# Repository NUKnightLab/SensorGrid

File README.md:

# Knight Lab SensorGridPM

Wireless particulate matter monitoring over LoRa networks

This is a version of the SensorGrid project that is specific to monitoring
particulate matter data (PM 2.5 and PM 10) and collecting that data over a
LoRa wireless network.

## Development

This code is structured for development in PlatformIO with its entry point set
to enable Arduino IDE compilation as well. See below for information about
compiling with the Arduino IDE.

### Dependencies

See the `lib_deps` section of the `platformio.ini` file

### Arduino IDE

Development is mostly done on PlatformIO (https://platformio.org/) but we do
occasional checks to ensure deployment on Arduino IDE. It should just work.

### Code Style

Please lint with cpplint before submitting code changes:

See this project's `CPPLINT.cfg` file for details about flags used for linting.
```
cpplint <SubProject>/*
```

We are making an effort to move toward the Google C++ style guide:
https://google.github.io/styleguide/cppguide.html

with some notable exceptions:

#### include subdirs not required

The requirement for specifying subdirs adds unnecessary complexity to project
maintenance. We use a relatively flat code structure within a given project,
thus includes will either be in the form `"file.h"` where file.h is in the
same directory or `<Library.h>` where Library is accessible on the compile path.

As a result, please lint with `--filter=-build/include_subdir`

#### naming conventions

 * Variables should be `snake_case`
 * Functions and methods should be `camelCase` (Not PascalCase)

## Troubleshooting

### The device goes into time-setting mode without pressing the time set button

The battery or solar subsystem must be plugged in for the device to start up in the standard runtime mode.

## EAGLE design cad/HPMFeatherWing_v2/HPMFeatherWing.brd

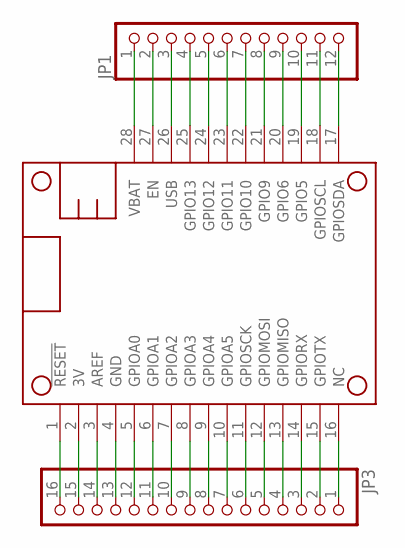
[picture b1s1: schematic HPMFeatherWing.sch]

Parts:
JP1: HEADER-1X1276MIL; 1X12_ROUND_76MIL
JP3: HEADER-1X16_76MIL; 1X16_ROUND_76MIL
MS1: FEATHERWING

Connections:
3V: JP3.15, MS1.2 (3V)
AREF: JP3.14, MS1.3 (AREF)
unnamed: JP1.2, MS1.27 (EN)
unnamed: JP3.1, MS1.16 (NC)
unnamed: JP1.4, MS1.25 (GPIO13)
unnamed: JP3.4, MS1.13 (GPIOMISO)
unnamed: JP3.5, MS1.12 (GPIOMOSI)
unnamed: JP3.6, MS1.11 (GPIOSCK)
unnamed: JP3.7, MS1.10 (GPIOA5)
unnamed: JP3.8, MS1.9 (GPIOA4)
unnamed: JP3.9, MS1.8 (GPIOA3)
unnamed: JP3.10, MS1.7 (GPIOA2)
unnamed: JP3.11, MS1.6 (GPIOA1)
unnamed: JP3.12, MS1.5 (GPIOA0)
unnamed: JP3.16, MS1.1 (!RESET)
unnamed: JP1.6, MS1.23 (GPIO11)
unnamed: JP1.7, MS1.22 (GPIO10)
unnamed: JP1.8, MS1.21 (GPIO9)
unnamed: JP1.9, MS1.20 (GPIO6)
unnamed: JP1.10, MS1.19 (GPIO5)
unnamed: JP1.11, MS1.18 (GPIOSCL)
unnamed: JP1.12, MS1.17 (GPIOSDA)
unnamed: JP3.3, MS1.14 (GPIORX)
unnamed: JP3.2, MS1.15 (GPIOTX)
unnamed: JP3.13, MS1.4 (GND)
unnamed: JP1.5, MS1.24 (GPIO12)
USB: JP1.3, MS1.26 (USB)
VBAT: JP1.1, MS1.28 (VBAT)

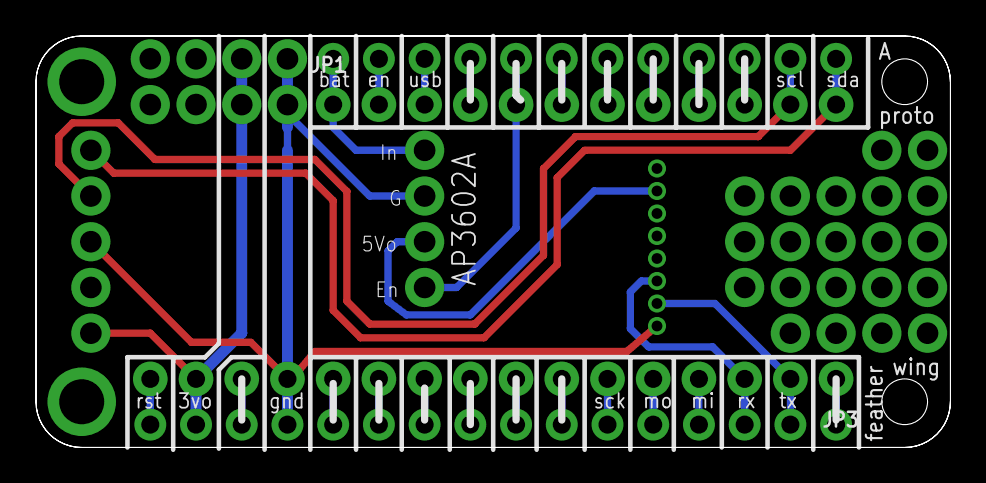
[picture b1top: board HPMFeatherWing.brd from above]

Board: 2 copper layers, 50.8 x 22.9 mm, 3 parts (0 on the bottom side), 28 nets.

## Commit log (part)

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2018-02-14 rtc begin first thing in setup
2018-02-14 reduce max nodes
2018-02-14 removed newline
2018-02-14 turn off wait for serial
2018-02-14 fix formatting of received message print
2018-02-14 log sent control
2018-02-14 removes blank line
2018-02-14 missing newline
2018-02-14 print NONE if no uncollected nodes
2018-02-14 logging cleanup
2018-02-15 fix pending node handling
2018-02-15 start of ditching auto-discovery
2018-02-15 no more auto-discovery
2018-02-16 buffer time for taking data samples
2018-02-16 don't use listen LED
2018-02-16 print out listen indicator; turns off data sampling and oled updates
2018-02-16 don't send control
2018-02-16 new SensorGrid.ino from scratch gets display working
2018-02-16 removes unused battery update thread (now in the display update)
2018-02-16 gets basic message send example working
2018-02-16 send period data collection request
2018-02-16 removes len from Message struct
2018-02-16 static malloc of the send Message space
2018-02-16 send collection request includes message id for each node - 0 for now
2018-02-16 adds array for last record ids
2018-02-16 try to fix iteration of dta record
2018-02-17 fix data iteration
2018-02-17 send new data back to 1
2018-02-17 try all next nodes before falling back to collector
2018-02-17 use low slow mode
2018-02-17 adds preferred routing order; replaces mesh router with static router
2018-02-17 routes to collector via from if no valid route exists
2018-02-17 print from before process_message call
2018-02-17 -> not .
2018-02-17 print add route to collector
2018-02-17 clear the receive buffer before receiving data
2018-02-17 turn off low and slow
2018-02-17 adds collector_process_message
2018-02-17 turns on cad
2018-02-18 spelling
2018-02-18 adds rh 1.8.2 tar
2018-02-18 timeout instead of protothread for display update
2018-02-18 set retries to 0
2018-02-18 send next activity after collection cycle
2018-02-18 turn off wait serial
2018-02-18 add self battery to new data
2018-02-18 rewrites node process data
2018-02-18 use constant MAX_NODES to create an ordered node array -- not a variable
2018-02-18 ordering is clobbering new data; use next_nodes for now
2018-02-18 include data type when adding battery level
2018-02-18 include max record id when adding self data
2018-02-18 track received record ids
2018-02-18 iterate to process data on collector
2018-02-18 update last dust sample time
2018-02-19 adds timestamp to sharp data
2018-02-19 use unixtime for dust timestamp
2018-02-19 loop through records for a node
2018-02-19 attempts to keep record collection under max data length
2018-02-19 comments removed
2018-02-19 print flags before send
2018-02-19 temp reduce max data length by 100
2018-02-19 change historical data head tracking
2018-02-19 set the max historical data id in the send data
2018-02-19 simplify historical data extraction
2018-02-19 check historical data based on the queue size
2018-02-19 turn off data sampling and oled updates
2018-02-19 increase hist data size
2018-02-19 debug printing of historical data traversal
2018-02-19 correct traversal index in log print
2018-02-19 missing condition check on printing out remaining historical data status
2018-02-19 print id of send to dest
2018-02-20 oled update back in
2018-02-20 attempt to avoid repeated data after a historical data shift
2018-02-20 missing in 50pct util case on collector
2018-02-20 fix string formatting of dust value print
2018-02-20 fix index of sharp dust struct in collector process
2018-02-20 use sharp dust struct for sending data
2018-02-20 fix record count and max id when adding sharp dust data
2018-02-20 insert sharp dust data as struct into new data
2018-02-20 struct for battery level
2018-02-20 50% data hist warn struct
2018-02-20 next activity seconds struct
2018-02-20 removes old approach to sending next activity
2018-02-20 attempt to manage collection via struct
2018-02-21 working on fixes to struct based data transfer. still not working right
2018-02-22 data record struct
2018-02-22 cleanup record set construction in send data col req
2018-02-25 move protocol.c into main program as protocol.cpp
2018-02-25 beginning of node handling of new protocol format
2018-02-27 basic node message processing working again
2018-02-27 new implementation of send next activity
2018-03-07 Adds honeywell pm sensor code into sub-project folder
2018-03-07 beginning of data serialization using arduinojson
2018-03-10 recording received ids
2018-03-13 clean history of acked messages; fix clobbering of copied data
2018-03-13 remove explicit routes
2018-03-19 basic serialization working
2018-03-19 borken seriousalization
2018-03-20 prevent json buffer overrun
2018-03-21 serialization but data buffer trimming not working
2018-03-23 adds EEPROM poc
2018-04-03 oled display of time; low power mode between sample cycles
2018-04-03 eeprom random test and byte test
2018-04-04 wait for data when reading
2018-04-04 continuously read and clear data on peripheral
2018-04-04 print stuff
2018-04-04 peripheral should read-only
2018-04-04 fix to reading cycle
2018-04-04 track rec w/ bit array
2018-04-04 clear data
2018-04-04 clarify read cycle
2018-04-04 all the pages
2018-04-09 module sets a random time for trc com testing
2018-04-11 5 minute sample period
2018-04-18 adds watchdog
2018-04-18 removes timer.h include
2018-04-18 parses logging data out of json from sensor module
2018-04-24 moves sensors lib source into src; adds properties
2018-04-25 starting attempt at linting w cpplint; moves PM into KnightLab_SensorGrid for better organization & linting
2018-05-04 baseline communication of PM to new collector
2018-05-04 remove vscode garbage
2018-05-04 gitignore vscode garbage
2018-05-07 char data in Message struct
2018-05-08 successfully sending json message over LoRa
2018-05-11 sending data list payloads to API w/ battery level
2018-05-14 api post changes; hpm key on honeywell vs data key
2018-05-14 bat data not quoted
2018-05-15 do standby; set clock
2018-05-15 post to networks api endpoint
2018-05-16 moves core codebase into root and old code into legacy for now
2018-05-18 adds in radio sleep; disable boost converter w/ en pin on 12
2018-05-30 aggregates data, logs just 1x per hour; logs json objects vs csv
2018-06-01 turn on standby
2018-06-04 next_period_time -> getNextPeriodTime
2018-06-04 set_init_timeout -> setInitTimeout
2018-06-04 set_sample_timeout -> setSampleTimeout
2018-06-04 record_data_samples -> recordDataSamples
2018-06-04 flash_heartbeat -> flashHeartbeat
2018-06-05 adds gps based clock update
2018-06-12 separates sd logging and tx code; fixes hpm data values
2018-06-12 standby on; tx on; logging off
2018-06-13 cleanup
2018-06-18 implements runtime watchdog
2018-06-19 adds startup branding splash
2018-06-20 adds Si7021 temp & humidity breakout support
2018-06-25 Adds watchdog modules and removes ASFcore dependency for TC3_Handler conflicts
2018-06-26 CPPLinting. Changes sprintf to snprintf which requires buffer size.
2018-06-26 changes DATASAMPLESIZE_DATASIZE to DATASAMPLE_DATASIZE
2018-06-26 snprintf format floats with f
2018-06-26 don't setup if testing
2018-06-27 Implemented sensor API for honeywell and humidty/temp
2018-06-27 adds changelog
2018-06-27 fixes si7021 setup declaration
2018-06-27 sensorconfig. Doesn't compile
2018-06-27 compiles
2018-06-27 doesn't compile
2018-06-27 fix sensor_config_head declr
2018-06-27 Sensorconfig working
2018-06-27 update changelog
2018-06-28 fixes runtime exceptions in sensor handling
2018-06-28 changelog
2018-06-29 Made small changes like clarifying variable names, declaring some structs in header files, and replacing serial.print with log_
2018-06-29 appends data to datalog file
2018-06-29 implements 2-tiered battery threshold; adds averaged battery reads; fixes interrupt race conditions where interrupt timeouts are actually before the current time
2018-07-02 set proper battery threshold
2018-07-02 Sensors are now classes rather than namespaces. Refactored sensor code from config into own file
2018-07-02 forces standby into wait mode after max of heartbeat period
2018-07-03 set hpm sample delay to 1 sec
2018-07-04 adds hpm featherwing cad files
2018-07-05 resolve conflicts
2018-07-05 instantiated sensor class configs compiling
2018-07-05 moves sensors module into sensors library and factors the base into separate interface and config
2018-07-05 Adds date in ISO 8601 format for datalog files. Also deletes files older than a max file age set to 5 days
2018-07-05 removes old sensor module
2018-07-05 removes commented databuf line
2018-07-05 check if old logfile exists before deleting
2018-07-05 v0.5 changelog date
2018-07-06 Factors configs into multi inherited structs
2018-07-10 Implements Set time option for external rtc
2018-08-16 Logfile parsers
    Parsers to format data from the log files to CSV
2018-08-17 Typo on #05
2018-10-24 Second node does not receive sent message from first node
2018-11-02 Sent message bytes different than received message bytes
2019-02-11 adds missing cad files
2019-02-11 Adds task scheduler library
2019-02-11 radio config tweaks
2019-02-12 adds (failing) test for lora setup
2019-02-13 adds transmitData to logging runtime
2019-02-20 comment out old tests
2019-04-11 beginning of collection request send/receive
2019-04-15 route requests still not working
2019-05-16 Trains a linear regression model for calibration
2019-07-18 recording data via data manager; 5 second heartbeat
2019-07-19 distinguish btwn system uptime and runtime
2019-07-19 fixes runtime & uptime reporting; turns off clock set check
2019-07-23 use rtcz from LoRaHarvest library
2019-07-25 collector running with modified LoRa library but freezes on tx
2019-07-25 missing deps
2019-07-25 call wifi end after setup to avoid LoRa conflict
2019-07-26 first attempt at posting data via wifi. currently receiving 400 from server
2019-08-01 old state managed runtime no longer used
2019-08-01 new runtime integration without explicit radio standby
2019-08-06 pulls up receive handlers: prep for factoring in sleep handler
2019-08-06 cleanup commented collector code
2019-08-06 collector specific handle packet
2019-08-06 cleanup factorings
2019-08-06 factor collector sendStandby
2019-08-09 fixes API bus sharing of LoRa and WiFi
2019-08-09 lora idle, not sleep
2019-08-19 moves platform.ini to example
2019-08-19 gitignore platform.ini
2019-08-19 factors wifi into separate module
2019-08-20 mark is collector
2019-08-20 use consolidated receive handler
2019-08-29 implements time sync on dest node w/ upstream collector
2019-08-29 adds NTP time setting on collector
2019-09-03 changes routes api endpoint to nodes
2019-09-03 parses routes from API
2019-09-04 improved collector runtime times out data requests and tracks unreachable nodes
2019-09-04 adds tx power to protocol header
2019-09-04 initializes tx power values on sensor nodes
2019-09-05 unused read node id from resistor value
2019-09-05 records restart; loads node id from lsb of Si7021 serialno if not in config
2019-09-06 cleanup collector code
2019-09-06 remove aunit from ini example
2019-09-06 fixes config of node id from sd card
2019-09-06 fixes lora config for no sd card present
2019-09-10 update tx power reporting nodes from sensor nodes
2019-09-13 implements queue based data recording and chunked transfer of data to api
2019-09-13 adds nginx config note for chunked transfer encoding
2019-09-17 adds an empty records queue for releasing used record structs into; fixes memory leak from unreleased historical records
2019-11-01 Bump werkzeug from 0.12.1 to 0.15.3 in /legacy
    Bumps [werkzeug](https://github.com/pallets/werkzeug) from 0.12.1 to 0.15.3.
    - [Release notes](https://github.com/pallets/werkzeug/releases)
    - [Changelog](https://github.com/pallets/werkzeug/blob/master/CHANGES.rst)
    - [Commits](https://github.com/pallets/werkzeug/compare/0.12.1...0.15.3)
